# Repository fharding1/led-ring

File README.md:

# LED Ring

A bright voltage regulated LED ring for vision tracking in FRC.

Copyright Franklin Harding 2020.

This source describes Open Hardware and is licensed under the CERN-OHL-Pv2

You may redistribute and modify this documentation and make products using it under the terms of the CERN-OHL-P v2 (https:/cern.ch/cern-ohl).This documentation is distributed WITHOUT ANY EXPRESS OR IMPLIED WARRANTY, INCLUDING OF MERCHANTABILITY, SATISFACTORY QUALITY AND FITNESS FOR A PARTICULAR PURPOSE. Please see the CERN-OHL-P v2 for applicable conditions

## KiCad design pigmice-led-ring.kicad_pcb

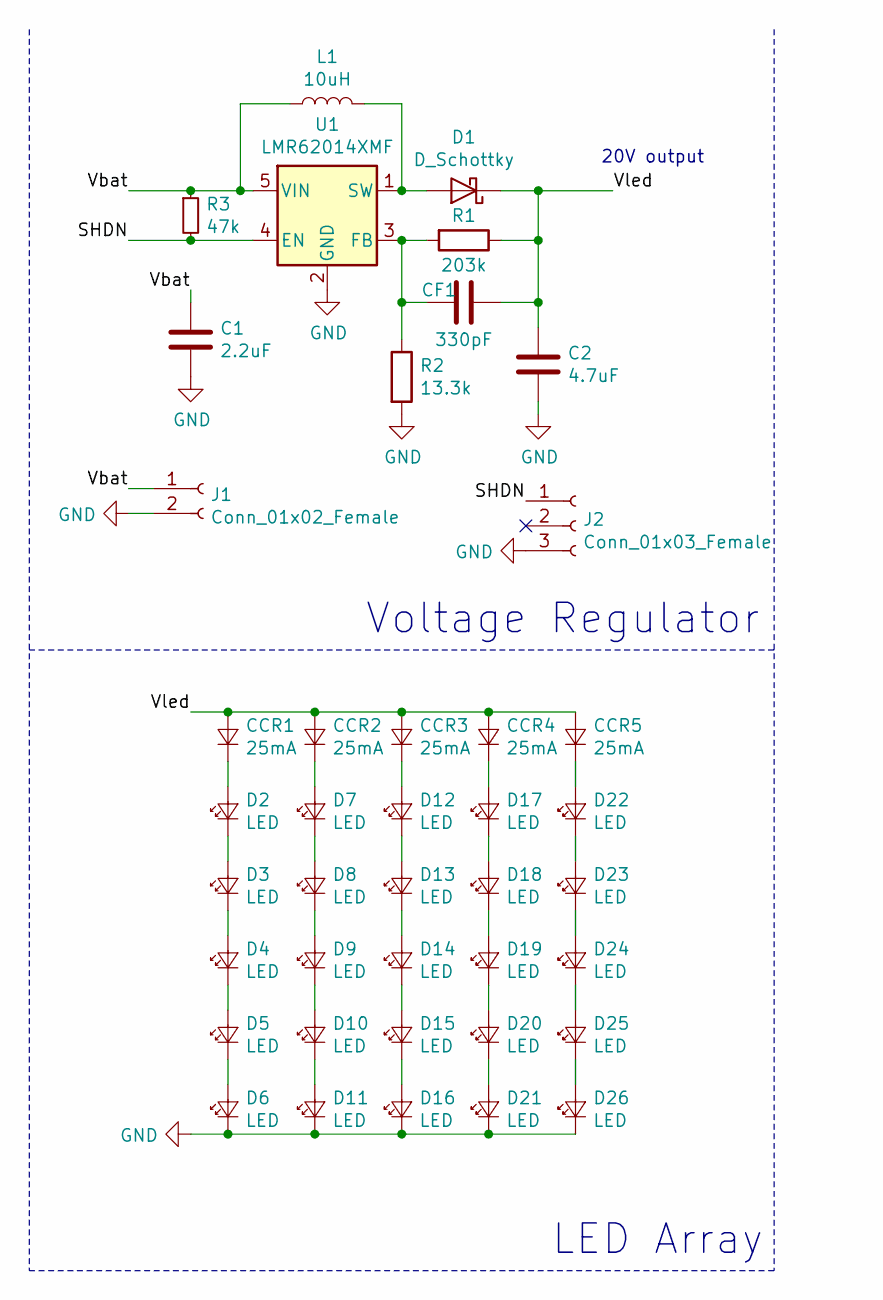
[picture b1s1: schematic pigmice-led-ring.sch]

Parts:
C1: 2.2uF; C_0805_2012Metric
C2: 4.7uF; C_0805_2012Metric
CCR1, CCR2, CCR3, CCR4, CCR5: 25mA; D_SOD-123
CF1: 330pF; C_0805_2012Metric
D1: D_Schottky; D_SOD-123
D2, D3, D4, D5, D6, D7, D8, D9, D10, D11, D12, D13, D14, D15, D16, D17, D18, D19, D20, D21, D22, D23, D24, D25, D26: LED; LED_Avago_PLCC4_3.2x2.8mm_CW
J1: Conn_01x02_Female; 45A-VERT-PAIR
J2: Conn_01x03_Female; PinHeader_1x03_P2.54mm_Vertical
L1: 10uH; L_Taiyo-Yuden_NR-24xx
R1: 203k; R_0805_2012Metric
R2: 13.3k; R_0805_2012Metric
R3: 47k; R_0805_2012Metric
U1: LMR62014XMF; SOT-23-5

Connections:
/SHDN: J2.1, R3.2, U1.4 (EN)
/Vbat: C1.1, J1.1, L1.1, R3.1, U1.5 (VIN)
/Vled: C2.1, CCR1.2 (A), CCR2.2 (A), CCR3.2 (A), CCR4.2 (A), CCR5.2 (A), CF1.2, D1.1 (K), R1.1
GND: C1.2, C2.2, D6.1 (K), D11.1 (K), D16.1 (K), D21.1 (K), D26.1 (K), J1.2, J2.3, R2.2, U1.2 (GND)
unnamed: CCR1.1 (K), D2.2 (A)
unnamed: CCR2.1 (K), D7.2 (A)
unnamed: CCR3.1 (K), D12.2 (A)
unnamed: CCR4.1 (K), D17.2 (A)
unnamed: CCR5.1 (K), D22.2 (A)
unnamed: CF1.1, R1.2, R2.1, U1.3 (FB)
unnamed: D1.2 (A), L1.2, U1.1 (SW)
unnamed: D2.1 (K), D3.2 (A)
unnamed: D3.1 (K), D4.2 (A)
unnamed: D4.1 (K), D5.2 (A)
unnamed: D5.1 (K), D6.2 (A)
unnamed: D7.1 (K), D8.2 (A)
unnamed: D8.1 (K), D9.2 (A)
unnamed: D10.1 (K), D11.2 (A)
unnamed: D9.1 (K), D10.2 (A)
unnamed: D12.1 (K), D13.2 (A)
unnamed: D13.1 (K), D14.2 (A)
unnamed: D14.1 (K), D15.2 (A)
unnamed: D15.1 (K), D16.2 (A)
unnamed: D17.1 (K), D18.2 (A)
unnamed: D18.1 (K), D19.2 (A)
unnamed: D19.1 (K), D20.2 (A)
unnamed: D20.1 (K), D21.2 (A)
unnamed: D22.1 (K), D23.2 (A)
unnamed: D23.1 (K), D24.2 (A)
unnamed: D24.1 (K), D25.2 (A)
unnamed: D25.1 (K), D26.2 (A)

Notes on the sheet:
20V output
Voltage Regulator
LED Array

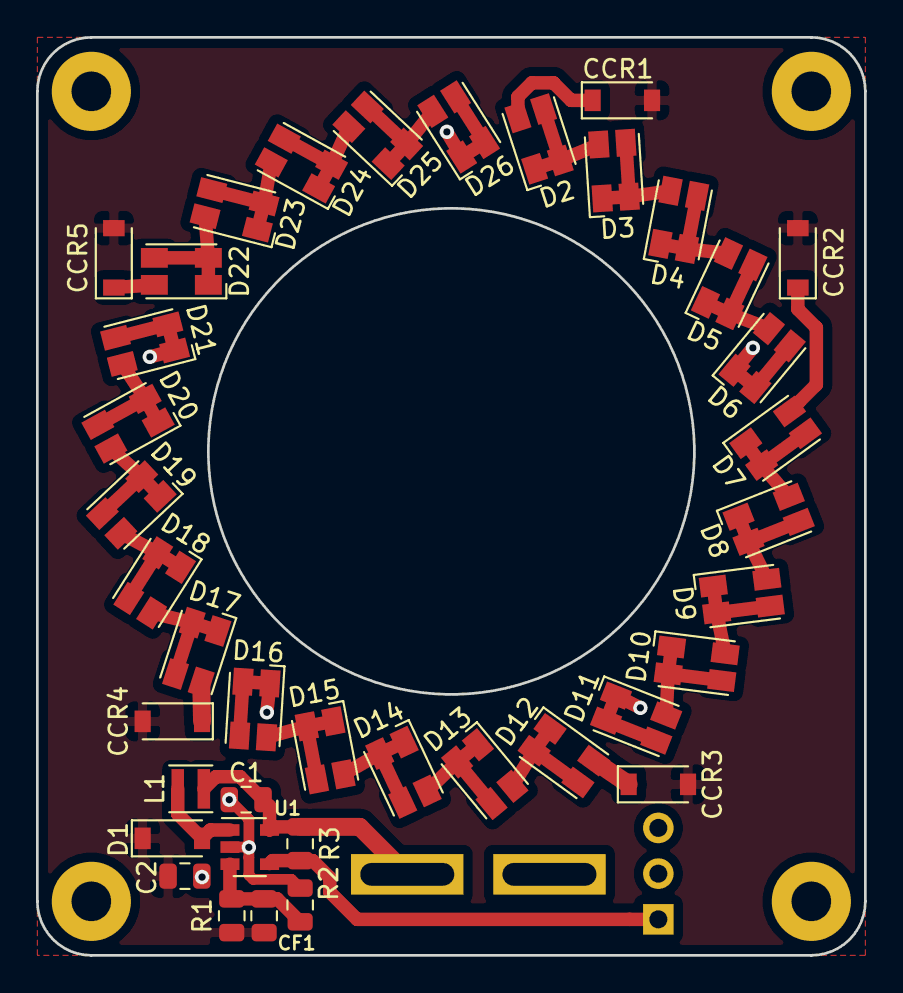
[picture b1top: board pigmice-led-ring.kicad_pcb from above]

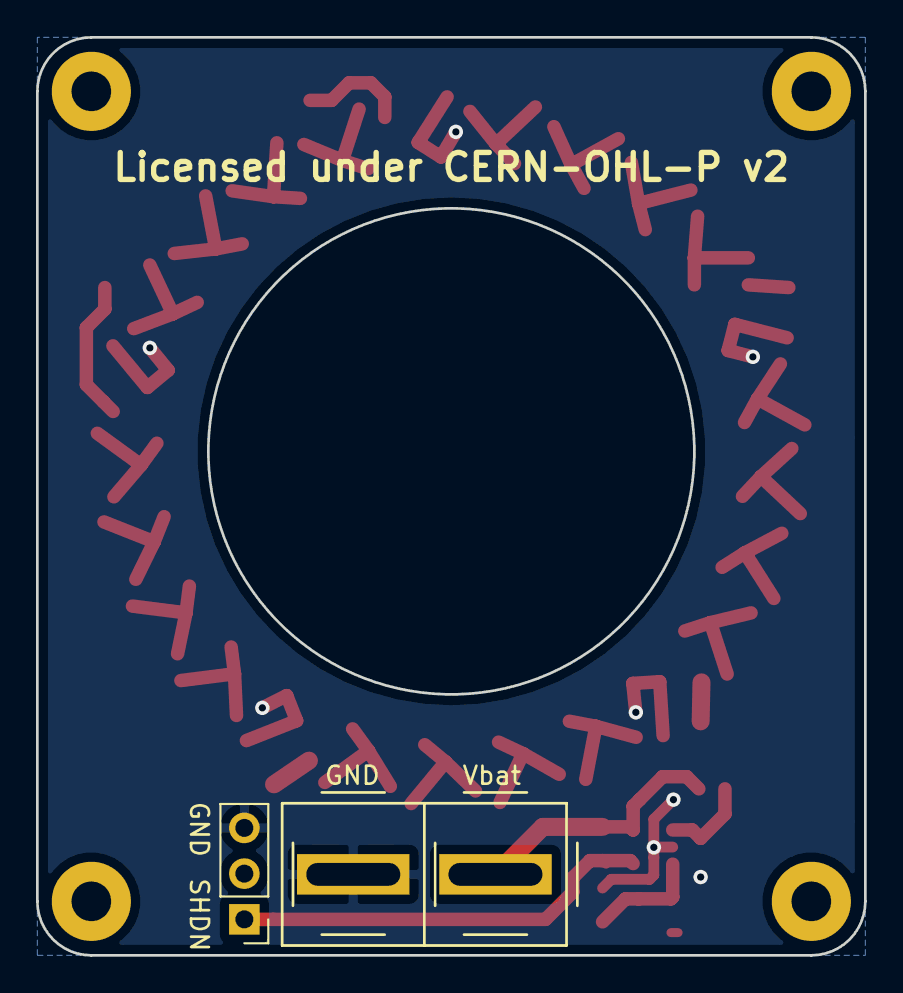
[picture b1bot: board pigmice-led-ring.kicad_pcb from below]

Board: 2 copper layers, 46.0 x 51.0 mm, 41 parts (2 on the bottom side), 31 nets.

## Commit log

2020-01-08 Initial KiCAD files
2020-01-08 Add README, 22ohm -> 82ohm
2020-01-08 Add photo to README
2020-01-08 Add input voltage and power consumption to README
2020-01-08 Fix README formatting
2020-01-08 Add details for alternative resistors
2020-01-08 Add lumens and wavelength to readme
2020-01-10 rev0.2.0
    * Uses an RCD-24 LED driver for constant current
    * M2 mounting holes
    * Powerpole, PWM connector
    * Sweet graphics :sunglasses:
2020-01-14 WIP v0.3.0 work
2020-01-14 Cleanup voltage regulator circuit spacing
2020-01-14 Add sponsor logos
2020-01-14 Move LED vias out of underneath pad
2020-01-14 Fix R2/CF1 labels
2020-01-14 Center URS logo better
2020-01-15 Swap out inductor for smaller 2410 footprint
2020-01-15 Switch from 150 to 137 ohm resistors for LEDs
2020-01-15 Fix LED digikey urls in bom
2020-01-16 Use CCRs instead of resistors
2020-01-16 Move labels a bit
2020-01-16 Update picture
2020-01-16 Remove extraneous trace
2020-01-23 Revision 0.3.1
    - Fixes an issue in the LED footprint resulting in a short between the
    anode and cathode
    - Uses thicker traces where possible
    - Moves CCRs for better connections to Vled plane
2020-01-24 Consolidate BOM
2020-01-25 Add mini badge
2020-01-25 Add button to mini-badge
2020-01-28 Move SHDN and Vbat traces a bit
2020-02-01 Powerpole, DFM, optimize BOM
    * Optimizes BOM to use cheaper components (~$15 components per board)
    * Change power connector to use an Anderson connector
    * Some DFM (remove copper fill logo, center part)
2020-02-01 Move over powerpole/PWM connector a bit
2020-02-01 Remove photos, text
2020-04-16 Add CERN OHL v2 permissive license

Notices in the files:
pigmice-led-ring.kicad_pcb:
Licensed under CERN-OHL-P v2
